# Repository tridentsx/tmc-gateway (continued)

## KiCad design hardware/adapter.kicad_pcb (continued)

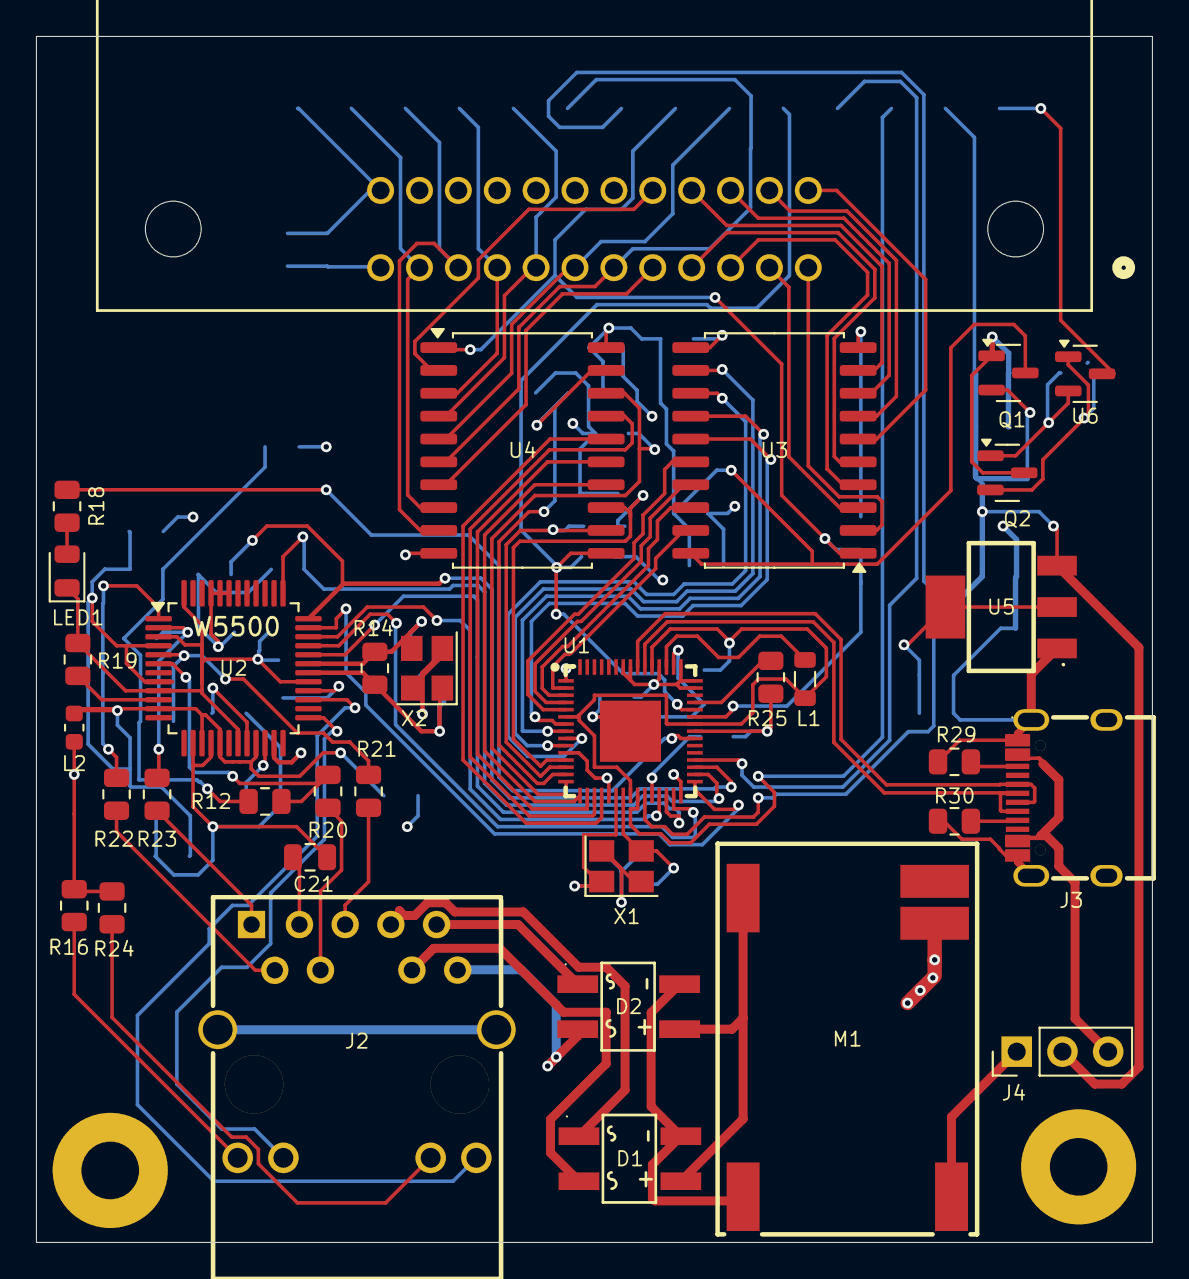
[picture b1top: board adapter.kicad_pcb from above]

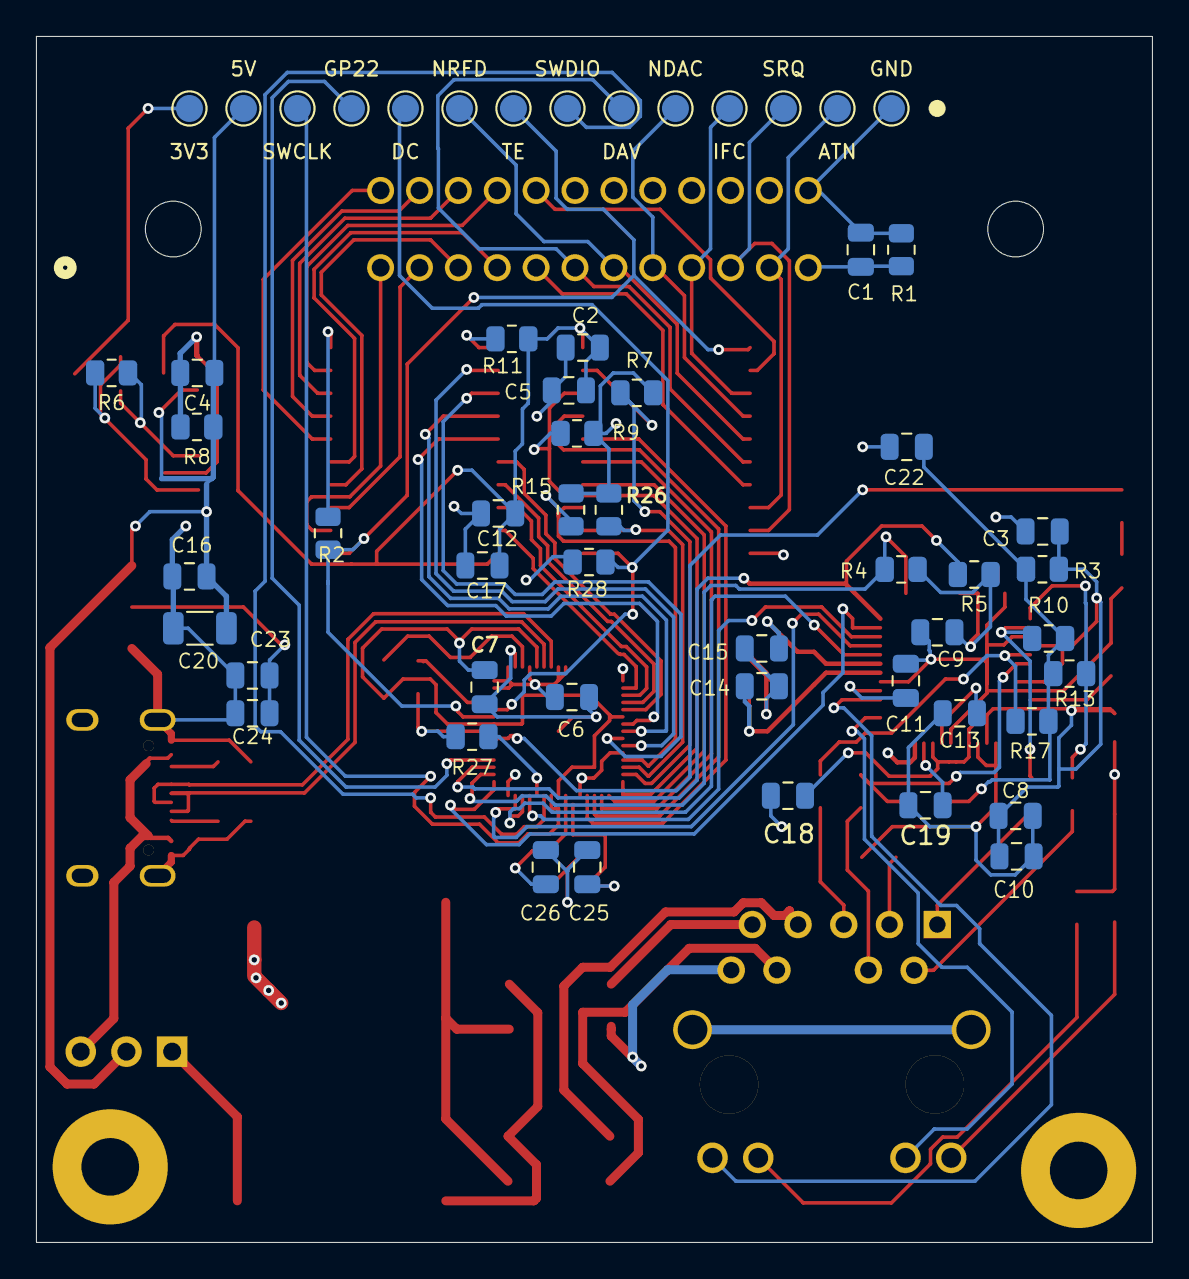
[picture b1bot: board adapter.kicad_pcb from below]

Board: 4 copper layers, 62.0 x 67.0 mm, 92 parts (56 on the bottom side), 91 nets.
